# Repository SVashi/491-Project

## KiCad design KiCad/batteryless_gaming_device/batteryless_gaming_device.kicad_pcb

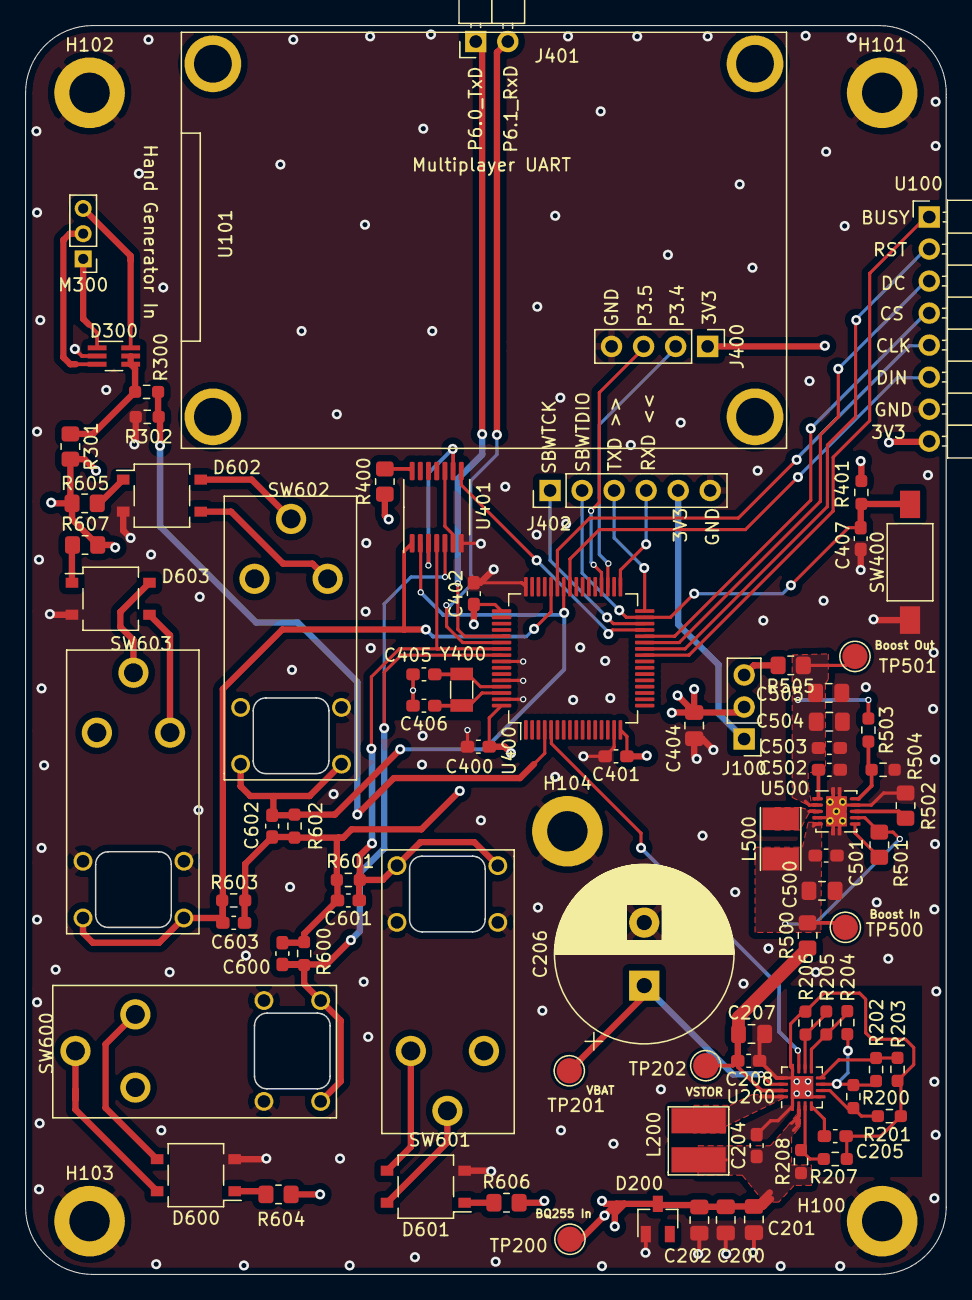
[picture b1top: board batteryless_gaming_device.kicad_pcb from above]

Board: 4 copper layers, 73.0 x 99.0 mm, 88 parts (0 on the bottom side), 64 nets.

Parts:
C200, C201, C202, C207, C404, C500, C504, C505: 10uF; C_0805_2012Metric_Pad1.18x1.45mm_HandSolder
C204: 4.7uF; C_0603_1608Metric_Pad1.08x0.95mm_HandSolder
C205: 0.01uF; C_0603_1608Metric_Pad1.08x0.95mm_HandSolder
C206: 220mF; CP_Radial_D14.0mm_P5.00mm
C208, C400, C401, C402, C501, C503: 0.1uF; C_0603_1608Metric_Pad1.08x0.95mm_HandSolder
C405, C406: 22pF; C_0603_1608Metric_Pad1.08x0.95mm_HandSolder
C407, C600, C601, C602, C603: 1nF; C_0603_1608Metric_Pad1.08x0.95mm_HandSolder
C502: 1uF; C_0603_1608Metric_Pad1.08x0.95mm_HandSolder
D200: BZX84Cxx; D_SOT-23_ANK_HandSoldering
D300: SDA006; SOT-363_SC-70-6_Handsoldering
D600, D601, D602, D603: D_Bridge_+-AA; TO-269AA
H100, H101, H102, H103, H104: MountingHole_Pad; MountingHole_3.2mm_M3_DIN965_Pad
J100: Voltage Source Select; PinHeader_1x03_P2.54mm_Vertical
J400: GPIO_breakout; PinHeader_1x04_P2.54mm_Vertical
J401: Multiplayer_Connector; PinHeader_1x02_P2.54mm_Horizontal
J402: Program_Header; PinHeader_1x06_P2.54mm_Vertical
L200: 22u; L_Wuerth-3816_6.3x6.3mm
L500: 2.2u; L_Taiyo-Yuden_NR-30xx_HandSoldering
M300: Hand Generator; PinHeader_1x03_P2.00mm_Vertical
R200: 5.62M; R_0603_1608Metric_Pad0.98x0.95mm_HandSolder
R201: 4.53M; R_0603_1608Metric_Pad0.98x0.95mm_HandSolder
R202: 0.39M; R_0603_1608Metric_Pad0.98x0.95mm_HandSolder
R203: 9.76M; R_0603_1608Metric_Pad0.98x0.95mm_HandSolder
R204: 1.69M; R_0603_1608Metric_Pad0.98x0.95mm_HandSolder
R205: 1.4M; R_0603_1608Metric_Pad0.98x0.95mm_HandSolder
R206: 6.98M; R_0603_1608Metric_Pad0.98x0.95mm_HandSolder
R207, R208: 10M; R_0603_1608Metric_Pad0.98x0.95mm_HandSolder
R300, R302, R503, R600, R601, R602, R603: 1M; R_0603_1608Metric_Pad0.98x0.95mm_HandSolder
R301, R400, R500, R501, R502, R505, R604, R605, R606, R607: 0; R_0805_2012Metric_Pad1.20x1.40mm_HandSolder
R401: 47k; R_0603_1608Metric_Pad0.98x0.95mm_HandSolder
R504: 180k; R_0603_1608Metric_Pad0.98x0.95mm_HandSolder
SW400: FSMSM; SW_SPST_FSMSM
SW600, SW601, SW602, SW603: EH_switch; EH_switch_v2
TP200, TP201, TP202, TP500, TP501: TestPoint; TestPoint_Pad_D2.0mm
U100: E-Ink_Display_1.54Inch; PinHeader_1x08_P2.54mm_Horizontal
U101: E-ink_Display_Outline; E-Ink_Display_1.54Inch
U200: BQ25504; VQFN-16-1EP_3x3mm_P0.5mm_EP1.8x1.8mm
U400: MSP430FR5994IPM; LQFP-64_10x10mm_P0.5mm
U401: SN74HCS32; TSSOP-14_4.4x5mm_P0.65mm
U500: TPS61201DRC; Texas_S-PVSON-N10_ThermalVias
Y400: ECS-.327-12.5-34R-C-TR; Crystal_SMD_3215-2Pin_3.2x1.5mm

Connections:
+3V3: C400.1, C401.1, C402.1, C404.1, C600.2, C601.2, C602.2, C603.2, J100.2, J400.1, R400.2, R401.1, R600.2, R601.2, R602.2, R603.2, U100.8, U400.16, U400.49, U400.64
/Button Generation/Button1: C603.1, R603.1, SW603.4, SW603.5, U400.44, U401.1
/Button Generation/Button2: C602.1, R602.1, SW602.4, SW602.5, U400.42, U401.2
/Button Generation/Button3: C601.1, R601.1, SW601.4, SW601.5, U400.55, U401.4
/Button Generation/Button4: C600.1, R600.1, SW600.4, SW600.5, U400.56, U401.5
/Microcontroller/GeneratorVcc: R300.1, R302.2, U400.4
/Microcontroller/P2.0_TXD: J402.3, U400.32
/Microcontroller/P2.1_RXD: J402.4, U400.33
/Microcontroller/P2.5: U100.4, U400.28
/Microcontroller/P2.6_OR_OUT: U400.29, U401.8
/Microcontroller/P3.4: J400.2, U400.35
/Microcontroller/P3.5: J400.3, U400.36
/Microcontroller/P4.1: U100.1, U400.25
/Microcontroller/P4.2: U100.2, U400.26
/Microcontroller/P4.3: U100.3, U400.27
/Microcontroller/P5.0: U100.6, U400.41
/Microcontroller/P5.2: U100.5, U400.43
/Microcontroller/P6.0_TxD: J401.1, U400.53
/Microcontroller/P6.1_RxD: J401.2, U400.54
/Microcontroller/SN_3A_IN: U401.3, U401.9
/Microcontroller/SN_3B_IN: U401.6, U401.10
/Microcontroller/TEST_SBWTCK: J402.1, U400.30
/Microcontroller/VBAT_OK: U200.11, U400.5
/Microcontroller/V_program: J100.1, J402.5
/Microcontroller/~RST~_SBWTDI0: C407.1, J402.2, R401.2, SW400.2, U400.31
/Power Regulation/Vin: C207.1, C208.1, R500.1, TP202.1, U200.15
/Power Regulation/Vout: J100.3, R505.2
/Power Storage/Vin: C200.1, C201.1, C202.1, C204.1, D200.1, L200.1, R208.1, R301.2, R604.2, R605.2, R606.2, R607.2, TP200.1, U200.2
GND: C200.2, C201.2, C202.2, C204.2, C205.2, C206.2, C207.2, C208.2, C400.2, C401.2, C402.2, C404.2, C405.2, C406.2, C407.2, C500.2, C501.2, C502.2, C503.2, C504.2, C505.2, D200.2, D300.2, D600.2, D601.2, D602.2, D603.2, H100.1, H101.1, H102.1, H103.1, H104.1, J400.4, J402.6, R201.2, R203.2, R206.2, R207.2, R302.1, R502.2, R504.2, SW400.1, SW600.6, SW600.7, SW601.6, SW601.7, SW602.6, SW602.7, SW603.6, SW603.7, U100.7, U200.1, U200.5, U200.12, U200.13, U200.17, U400.15, U400.48, U400.57, U400.60, U400.63, U401.7, U500.4, U500.9, U500.11
unnamed: C205.1, U200.4
unnamed: C206.1, TP201.1, U200.14
unnamed: C405.1, U400.61, Y400.2
unnamed: C406.1, U400.62, Y400.1
unnamed: C500.1, C501.1, L500.1, R500.2, R501.1, TP500.1, U500.5, U500.7
unnamed: C502.1, U500.1
unnamed: C503.1, C504.1, C505.1, R503.1, R505.1, TP501.1, U500.2
unnamed: D300.1, M300.1
unnamed: D300.3, M300.2
unnamed: D300.4, D300.5, R300.2, R301.1
unnamed: D300.6, M300.3
unnamed: D600.1, R604.1
unnamed: D600.3, SW600.1
unnamed: D600.4, SW600.3
unnamed: D601.1, R606.1
unnamed: D601.3, SW601.1
unnamed: D601.4, SW601.3
unnamed: D602.1, R605.1
unnamed: D602.3, SW602.1
unnamed: D602.4, SW602.3
unnamed: D603.1, R607.1
unnamed: D603.3, SW603.1
unnamed: D603.4, SW603.3
unnamed: L200.2, U200.16
unnamed: L500.2, U500.3
unnamed: R200.1, R202.1, R204.1, U200.7
unnamed: R200.2, R201.1, U200.6
unnamed: R202.2, R203.1, U200.8
unnamed: R204.2, R205.1, U200.9
unnamed: R205.2, R206.1, U200.10
unnamed: R207.1, R208.2, U200.3
unnamed: R400.1, U401.14
unnamed: R501.2, U500.6
unnamed: R502.1, U500.8
unnamed: R503.2, R504.1, U500.10

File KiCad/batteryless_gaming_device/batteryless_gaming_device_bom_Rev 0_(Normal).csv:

Component,References,Value,Quantity Per PCB,Footprint,DigiKey PN
1,C405 C406,22pF,2,C_0603_1608Metric_Pad1.08x0.95mm_HandSolder,311-4030-1-ND
2,C407 C600 C601 C602 C603,1nF,5,C_0603_1608Metric_Pad1.08x0.95mm_HandSolder,1276-CL10B102KB8WPJCCT-ND
3,C205,0.01uF,1,C_0603_1608Metric_Pad1.08x0.95mm_HandSolder,1276-CL10B103KB8WPJCCT-ND
4,C208 C400 C401 C402 C501 C503,0.1uF,6,C_0603_1608Metric_Pad1.08x0.95mm_HandSolder,311-1344-1-ND
5,C502,1uF,1,C_0603_1608Metric_Pad1.08x0.95mm_HandSolder,1276-1946-1-ND
6,C204,4.7uF,1,C_0603_1608Metric_Pad1.08x0.95mm_HandSolder,1276-1902-1-ND
,,,,,
8,C207 C404 C500 C504 C505,10uF,5,C_0805_2012Metric_Pad1.18x1.45mm_HandSolder,399-11939-1-ND
9,C206,220mF,1,CP_Radial_D14.0mm_P5.00mm,
10,D200,BZX84Cxx,1,D_SOT-23_ANK_HandSoldering,BZX84C4V3-FDICT-ND
11,D600 D601 D602 D603,D_Bridge_+-AA,4,TO-269AA,641-1213-1-ND
12,D300,SDA006,1,SOT-363_SC-70-6_Handsoldering,SDA006-7DICT-ND
13,J400,GPIO_breakout,1,PinHeader_1x04_P2.54mm_Vertical,
14,J401,Multiplayer_Connector,1,PinHeader_1x02_P2.54mm_Horizontal,
15,J402,Program_Header,1,PinHeader_1x06_P2.54mm_Vertical,
16,J100,Voltage Source Select,1,PinHeader_1x03_P2.54mm_Vertical,
17,L500,2.2u,1,L_Taiyo-Yuden_NR-30xx_HandSoldering,587-1648-1-ND
18,L200,22u,1,L_Wuerth-3816_6.3x6.3mm,732-1012-1-ND
19,M300,Hand Generator,1,PinHeader_1x03_P2.00mm_Vertical,A100097-ND
20,R301 R400 R500 R501 R502 R505 R604 R605 R606 R607,0,10,R_0805_2012Metric_Pad1.20x1.40mm_HandSolder,YAG3755CT-ND
21,R401,47k,1,R_0603_1608Metric_Pad0.98x0.95mm_HandSolder,RMCF0603JT47K0CT-ND
22,R504,180k,1,R_0603_1608Metric_Pad0.98x0.95mm_HandSolder,RMCF0603FT180KCT-ND
23,R202,0.39M,1,R_0603_1608Metric_Pad0.98x0.95mm_HandSolder,RMCF0603FT390KCT-ND
24,R300 R302 R503 R600 R601 R602 R603,1M,7,R_0603_1608Metric_Pad0.98x0.95mm_HandSolder,511-1820-1-ND
25,R205,1.4M,1,R_0603_1608Metric_Pad0.98x0.95mm_HandSolder,RMCF0603FT1M40CT-ND
26,R204,1.69M,1,R_0603_1608Metric_Pad0.98x0.95mm_HandSolder,541-1.69MHCT-ND
27,R201,4.53M,1,R_0603_1608Metric_Pad0.98x0.95mm_HandSolder,RMCF0603FT4M53CT-ND
28,R200,5.62M,1,R_0603_1608Metric_Pad0.98x0.95mm_HandSolder,RMCF0603FT5M62CT-ND
29,R206,6.98M,1,R_0603_1608Metric_Pad0.98x0.95mm_HandSolder,RMCF0603FT6M98CT-ND
30,R203,9.76M,1,R_0603_1608Metric_Pad0.98x0.95mm_HandSolder,541-9.76MHCT-ND
31,R207 R208,10M,2,R_0603_1608Metric_Pad0.98x0.95mm_HandSolder,541-2804-1-ND
32,SW600 SW601 SW602 SW603,EH_switch,4,EH_switch_v2,EG5982-ND
33,SW400,FSMSM,1,SW_SPST_FSMSM,450-1140-ND
34,U200,BQ25504,1,VQFN-16-1EP_3x3mm_P0.5mm_EP1.8x1.8mm,296-48495-1-ND
35,U100,E-Ink_Display_1.54Inch,1,PinHeader_1x08_P2.54mm_Horizontal,
36,U101,E-ink_Display_Outline,1,E-Ink_Display_1.54Inch,
37,U400,MSP430FR5994IPM,1,LQFP-64_10x10mm_P0.5mm,296-45560-1-ND
38,U401,SN74HCS32,1,TSSOP-14_4.4x5mm_P0.65mm,296-SN74HCS32PWRCT-ND
39,U500,TPS61201DRC,1,Texas_S-PVSON-N10_ThermalVias,296-21684-1-ND
40,Y400,ECS-.327-12.5-34R-C-TR,1,Crystal_SMD_3215-2Pin_3.2x1.5mm,XC2127CT-ND
,,,,,
,,,,,
,,,,,
,,,,,
,,,,,
Component Groups:,40,,,,
Component Count:,78,,,,
Fitted Components:,78,,,,
Number of PCBs:,1,,,,
Total components:,78,,,,
Schematic Version:,Rev 0,,,,
Schematic Date:,,,,,
PCB Variant:,normal,,,,
BoM Date:,11/18/2021 0:40,,,,
Schematic Source:,batteryless_gaming_device.sch,,,,
KiCad Version:,Eeschema (5.1.10)-1,,,,

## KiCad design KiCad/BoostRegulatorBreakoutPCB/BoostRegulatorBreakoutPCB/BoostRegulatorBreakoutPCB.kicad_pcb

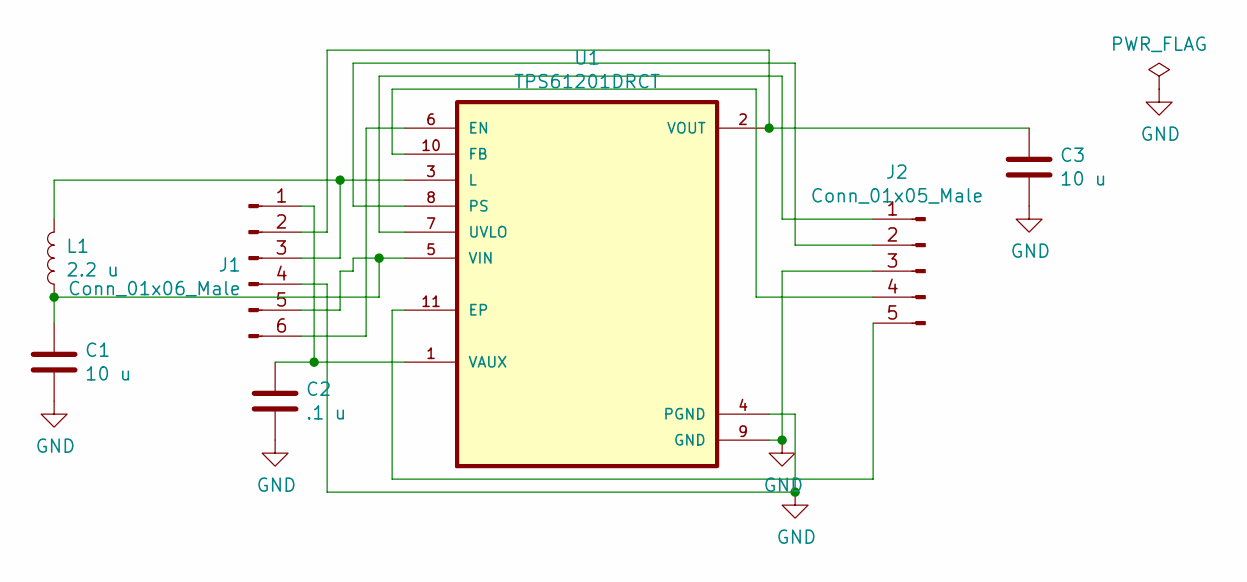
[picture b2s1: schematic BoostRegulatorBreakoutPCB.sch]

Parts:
C1, C3: 10 u; CP_Radial_D5.0mm_P2.50mm
C2: .1 u; CP_Radial_D5.0mm_P2.50mm
J1: Conn_01x06_Male; PinSocket_1x06_P2.54mm_Vertical
J2: Conn_01x05_Male; PinSocket_1x05_P2.54mm_Vertical
L1: 2.2 u; L_Axial_L5.0mm_D3.6mm_P10.00mm_Horizontal_Murata_BL01RN1A2A2
U1: TPS61201DRCT; DFN-10-1EP_3x3mm_P0.5mm_EP1.7x2.5mm_HandSolder

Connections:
GND: C1.2, C2.2, C3.2, J1.4, J2.3, U1.4 (PGND), U1.9 (GND)
unnamed: C1.1, J1.5, L1.1, U1.5 (VIN)
unnamed: C2.1, J1.1, U1.1 (VAUX)
unnamed: C3.1, J1.2, U1.2 (VOUT)
unnamed: J1.3, L1.2, U1.3 (L)
unnamed: J1.6, U1.6 (EN)
unnamed: J2.1, U1.7 (UVLO)
unnamed: J2.2, U1.8 (PS)
unnamed: J2.4, U1.10 (FB)
unnamed: J2.5, U1.11 (EP)

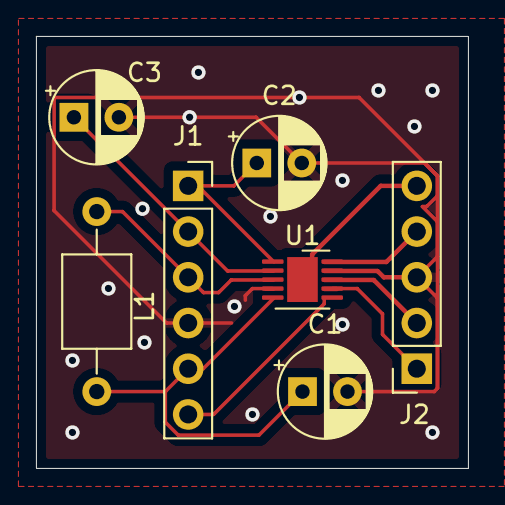
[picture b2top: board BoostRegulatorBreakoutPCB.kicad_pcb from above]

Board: 2 copper layers, 24.0 x 24.0 mm, 7 parts (0 on the bottom side), 10 nets.

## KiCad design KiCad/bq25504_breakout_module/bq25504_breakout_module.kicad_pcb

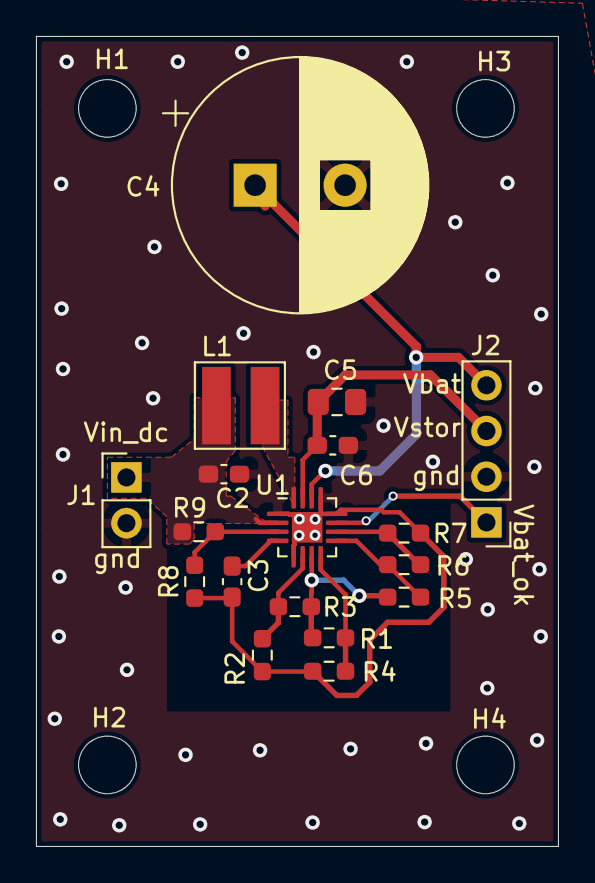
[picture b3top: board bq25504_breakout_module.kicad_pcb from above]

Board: 2 copper layers, 29.0 x 45.0 mm, 22 parts (0 on the bottom side), 13 nets.

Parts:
C2: 4.7uF; C_0603_1608Metric_Pad1.08x0.95mm_HandSolder
C3: 0.01uF; C_0603_1608Metric_Pad1.08x0.95mm_HandSolder
C4: 220mF; CP_Radial_D14.0mm_P5.00mm
C5: 10uF; C_0805_2012Metric_Pad1.18x1.45mm_HandSolder
C6: 0.1uF; C_0603_1608Metric_Pad1.08x0.95mm_HandSolder
H1, H2, H3, H4: MountingHole; MountingHole_3.2mm_M3
J1: Vin; PinHeader_1x02_P2.54mm_Vertical
J2: Output; PinHeader_1x04_P2.54mm_Vertical
L1: 22uH; L_Wuerth-3816_6.3x6.3mm
R1: 4.32M; R_0603_1608Metric_Pad0.98x0.95mm_HandSolder
R2: 5.6M; R_0603_1608Metric_Pad0.98x0.95mm_HandSolder
R3: 1.67M; R_0603_1608Metric_Pad0.98x0.95mm_HandSolder
R4: 8.25M; R_0603_1608Metric_Pad0.98x0.95mm_HandSolder
R5: 1.3M; R_0603_1608Metric_Pad0.98x0.95mm_HandSolder
R6: 2.7M; R_0603_1608Metric_Pad0.98x0.95mm_HandSolder
R7: 6.2M; R_0603_1608Metric_Pad0.98x0.95mm_HandSolder
R8, R9: 10M; R_0603_1608Metric_Pad0.98x0.95mm_HandSolder
U1: BQ25504; QFN-16-1EP_3x3mm_P0.5mm_EP1.7x1.7mm_HandSolder

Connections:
GND: C2.2, C3.2, C4.2, C5.2, C6.2, J1.2, J2.2, R2.2, R4.2, R7.2, R8.1, U1.1, U1.5, U1.12, U1.13, U1.17
unnamed: C3.1, U1.4
unnamed: C5.1, C6.1, J2.3, U1.15
unnamed: J2.1, U1.11
unnamed: L1.2, U1.16
unnamed: R1.1, R3.1, R5.1, U1.7
unnamed: R1.2, R2.1, U1.6
unnamed: R3.2, R4.1, U1.8
unnamed: R5.2, R6.1, U1.9
unnamed: R6.2, R7.1, U1.10
unnamed: R8.2, R9.2, U1.3
VBAT: C4.1, J2.4, U1.14
VDC: C2.1, J1.1, L1.1, R9.1, U1.2

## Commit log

2021-04-02 Proof of Concept
2021-04-02 Updated refresh rate
2021-04-02 Updated refresh rate and built
2021-09-05 created kicad folder
2021-09-05 test update
2021-09-05 moved part to test hub
2021-09-07 created bq25504 module/breakout board
2021-09-08 updated bq25504
2021-09-09 confirmed jakes breakout board layout
2021-09-30 updated some stuff
2021-11-14 updated some stuff in main schematic
2021-11-14 keep updating schematic
2021-11-14 keep on keeping on
2021-11-15 updated schematic
2021-11-17 just kinda out here guys ya know what im saying
2021-11-18 oh ya
2021-12-07 stuff
